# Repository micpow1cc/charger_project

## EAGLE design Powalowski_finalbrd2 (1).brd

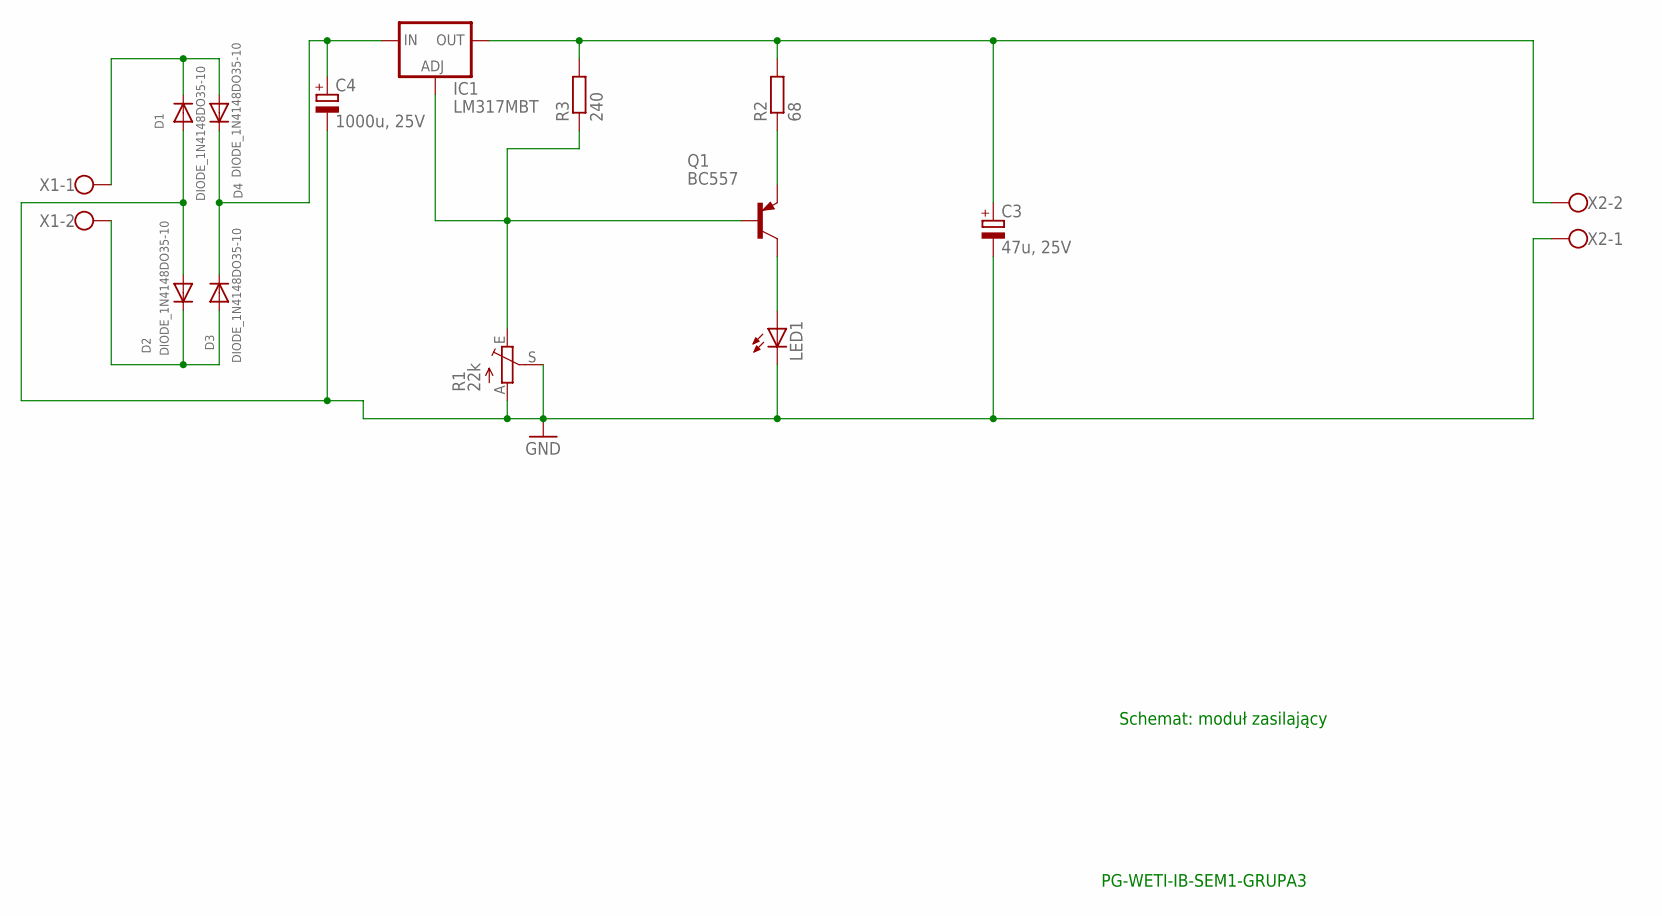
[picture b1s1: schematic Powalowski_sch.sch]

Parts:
C3: 47u, 25V; E7,5-16
C4: 1000u, 25V; E7,5-16
D1, D2, D3, D4: DIODE_1N4148DO35-10; DIODE_DO35-10
IC1: LM317MBT; TO220L1
LED1: LED_LED5MM
Q1: BC557; TO92-EBC
R1: 22k; RS3
R2: 68; R1210
R3: 240; R1210
X1, X2: W237-102

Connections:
unnamed: D1.C, D4.A, X1.1
unnamed: C3.-, C4.-, D1.A, D2.A, LED1.K (C), R1.A, R1.S, X2.1
unnamed: LED1.A, Q1.C
unnamed: C4.+, D3.C, D4.C, IC1.3 (IN)
unnamed: D2.C, D3.A, X1.2
unnamed: C3.+, IC1.2 (OUT), R2.2, R3.2, X2.2
unnamed: IC1.1 (ADJ), Q1.B, R1.E, R3.1
unnamed: Q1.E, R2.1

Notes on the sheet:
Schemat: moduł zasilający
PG-WETI-IB-SEM1-GRUPA3

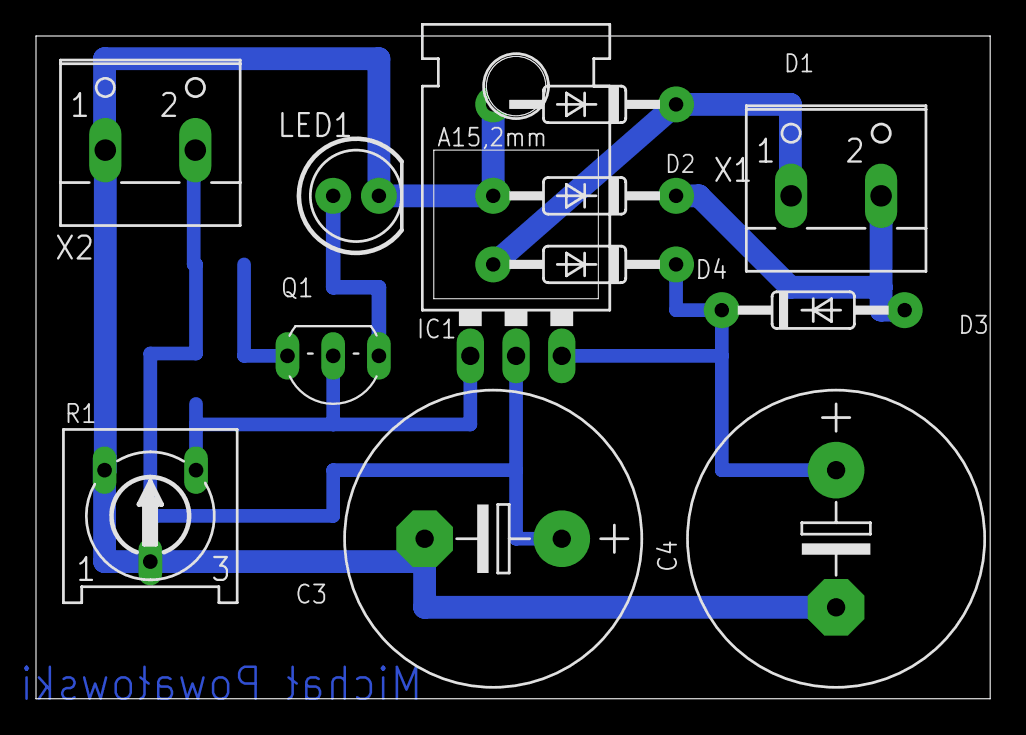
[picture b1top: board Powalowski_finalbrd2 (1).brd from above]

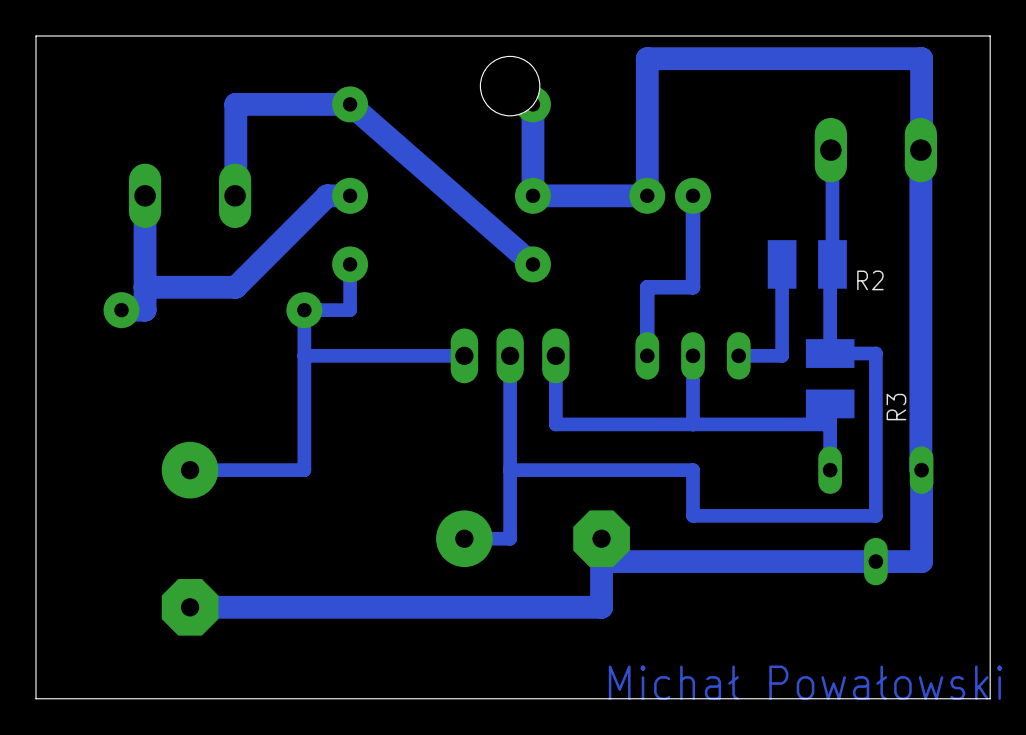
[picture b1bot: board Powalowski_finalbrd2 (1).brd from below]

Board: 2 copper layers, 53.0 x 36.8 mm, 14 parts (2 on the bottom side), 8 nets.
